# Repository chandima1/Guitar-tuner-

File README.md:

# Guitar-tuner-
This is a project based on ATmega 32A microcontroller.

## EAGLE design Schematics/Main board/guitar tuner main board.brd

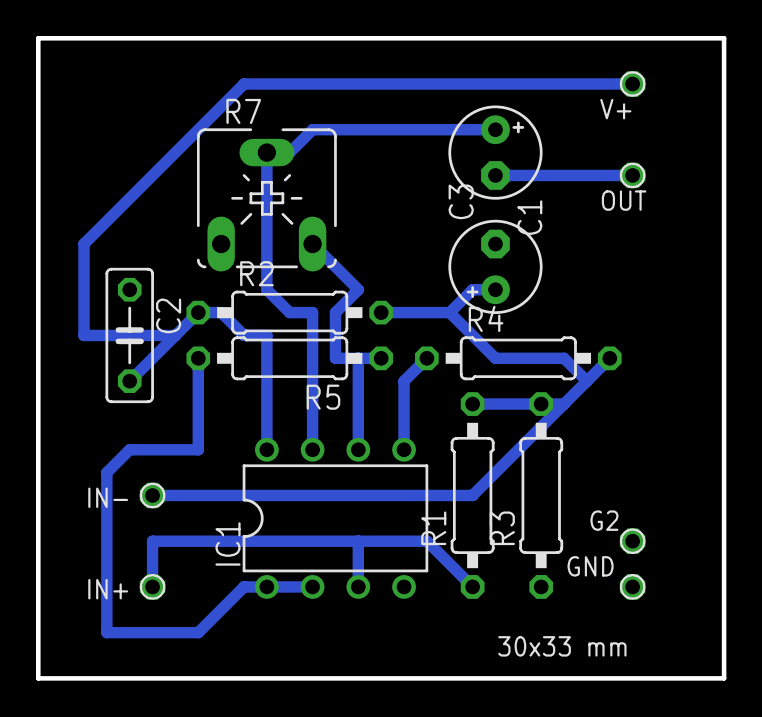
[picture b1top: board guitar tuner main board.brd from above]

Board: 2 copper layers, 38.1 x 35.6 mm, 16 parts (0 on the bottom side), 9 nets.

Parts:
C1, C3: 10u; E2,5-5
C2: 100n; C050-025X075
G2: PAD146
GND: PAD146
IC1: TLC272; DIL08
IN+: PAD146
IN-: PAD146
OUT: PAD146
R1: 10K..10M; 0207/10
R2: 150K; 0207/10
R3: 100K; 0207/10
R4, R5: 1K; 0207/10
R7: CA6V
V+: PAD146

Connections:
GND: C2.1, C3.-, G2.1, GND.1, IC1.4, R3.1, R7.A
unnamed: IC1.6, R5.1, R7.E
unnamed: C1.-, OUT.1
unnamed: IC1.5, R4.1
unnamed: C1.+, IC1.7, R7.S
unnamed: IC1.1, IC1.2, R5.2
unnamed: IC1.3, IN+.1, R1.1
unnamed: C3.+, IN-.1, R1.2, R2.2, R3.2, R4.2
V9V: C2.2, IC1.8, R2.1, V+.1
